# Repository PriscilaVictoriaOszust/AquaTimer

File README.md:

AquaTimer - Software

Desarrollado por: Victoria Oszust

Descripción

Esta carpeta contiene la documentación relacionada con el software del proyecto AquaTimer, un temporizador para la ducha diseñado para fomentar el ahorro de agua y promover el cuidado del medio ambiente.

Funcionamiento

El programa utiliza una Raspberry Pi Pico para controlar un anillo NeoPixel de 12 LEDs. Al iniciar el temporizador, las luces se encienden en verde y, a medida que transcurre el tiempo, se van apagando progresivamente. Cuando el tiempo finaliza, todos los LEDs se encienden en rojo.

Herramientas utilizadas

* Wokwi: plataforma de simulación de circuitos electrónicos.
* MicroPython: lenguaje de programación utilizado para controlar el microcontrolador.
* Raspberry Pi Pico: placa encargada de ejecutar el programa.

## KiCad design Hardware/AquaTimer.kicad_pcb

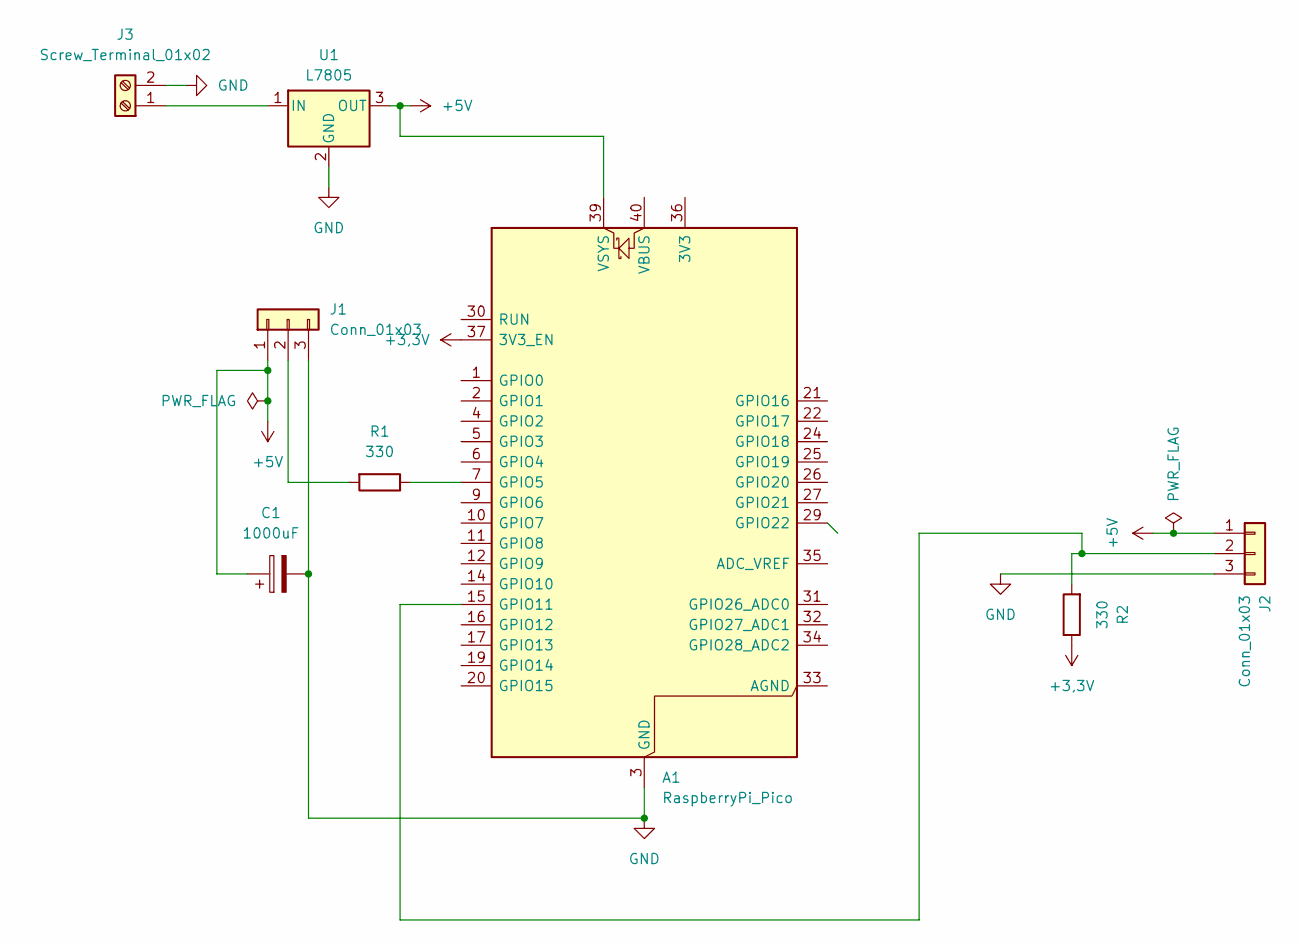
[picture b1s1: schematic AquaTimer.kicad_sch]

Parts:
A1: RaspberryPi_Pico; RaspberryPi_Pico_Common_THT
C1: 1000uF; CP_Radial_D10.0mm_P5.00mm
J1, J2: Conn_01x03; PinHeader_1x03_P2.54mm_Vertical
J3: Screw_Terminal_01x02; TerminalBlock_MaiXu_MX126-5.0-02P_1x02_P5.00mm
R1, R2: 330; R_Axial_DIN0207_L6.3mm_D2.5mm_P10.16mm_Horizontal
U1: L7805; TO255P1020X450X2000-3

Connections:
+3,3V: A1.37 (3V3_EN), R2.1
+5V: A1.39 (VSYS), C1.1, J1.1, J2.1, U1.3 (OUT)
GND: A1.3 (GND), A1.8 (GND), A1.13 (GND), A1.18 (GND), A1.23 (GND), A1.28 (GND), A1.38 (GND), C1.2, J1.3, J2.3, J3.2, U1.2 (GND)
unnamed: A1.7 (GPIO5), R1.1
unnamed: A1.15 (GPIO11), J2.2, R2.2
unnamed: J1.2, R1.2
unnamed: J3.1, U1.1 (IN)

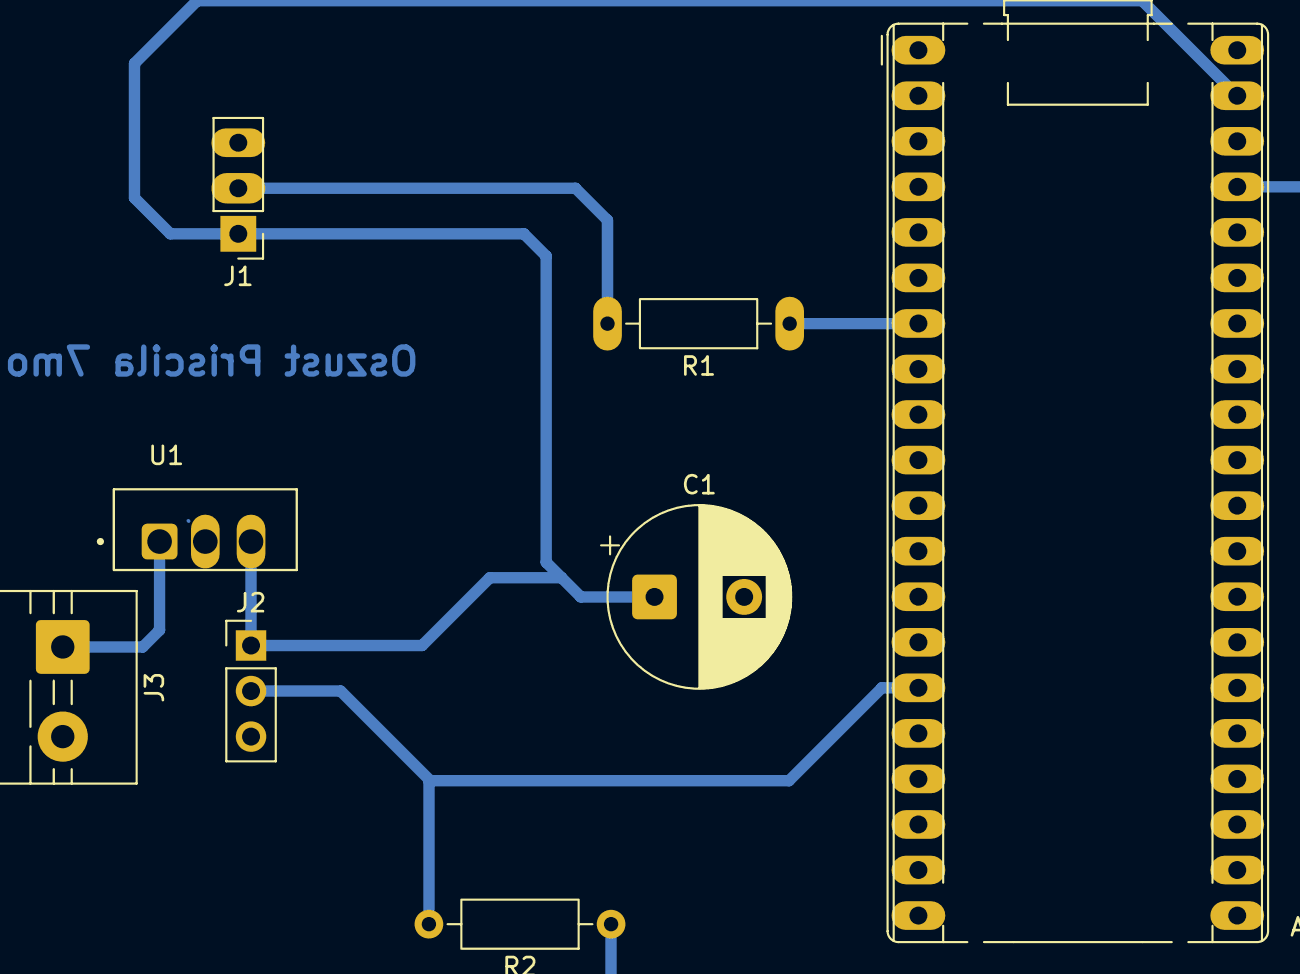
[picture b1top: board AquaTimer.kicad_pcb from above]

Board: 2 copper layers, 8 parts (0 on the bottom side), 7 nets.
